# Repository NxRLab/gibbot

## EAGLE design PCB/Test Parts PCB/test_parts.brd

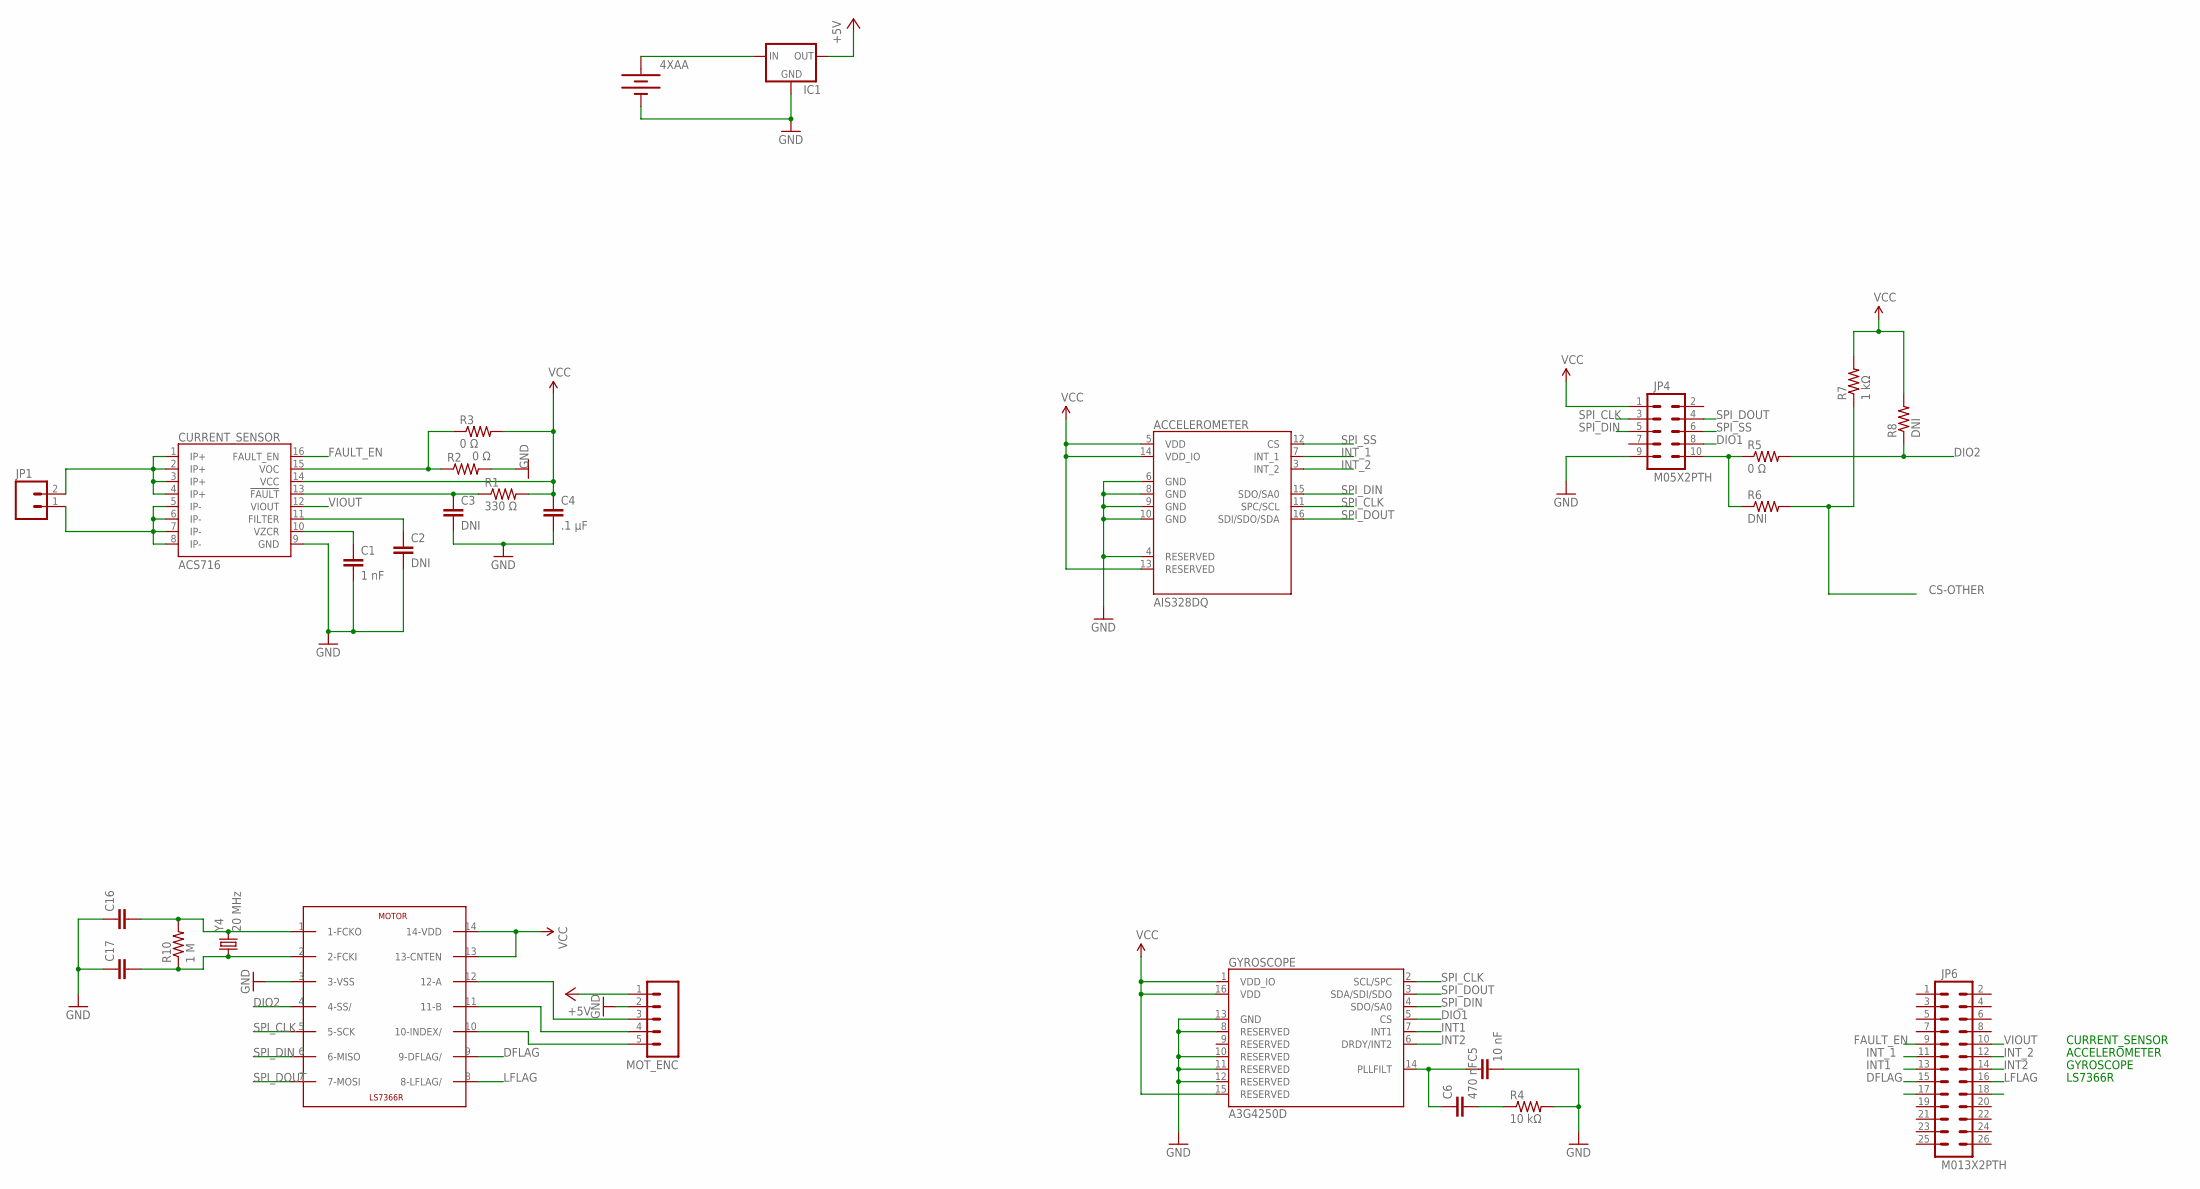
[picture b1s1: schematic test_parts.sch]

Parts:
4XAA: BATTERYTOP; BH4AA-PC
ACCELEROMETER: AIS328DQ; QFPN-24
C1: 1 nF; 0603-CAP
C2, C3: DNI; 0603-CAP
C4: .1 µF; 0603-CAP
C5: 10 nF; 0603-CAP
C6: 470 nF; 0603-CAP
C16, C17: CAP0603-CAP; 0603-CAP
CURRENT_SENSOR: ACS716; SOICW
GYROSCOPE: A3G4250D; LGA-16
IC1: V_REG_78XX-TO-220; TO-220-ALT
JP1: M02PTH; 1X02
JP4: M05X2PTH; AVR_ICSP
JP6: M013X2PTH; AVR_ICSP
MOTOR: LS7366R; SO14
MOT_ENC: M05PTH; 1X05
R1: 330 Ω; 0603-RES
R2, R3, R5: 0 Ω; 0603-RES
R4: 10 kΩ; 0603-RES
R6, R8: DNI; 0603-RES
R7: 1 kΩ; 0603-RES
R10: 1 M; R0603
Y4: 20 MHz; HC49US

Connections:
+5V: IC1.OUT, MOT_ENC.1
CS-OTHER: R6.2, R7.1
DFLAG: JP6.15, MOTOR.9 (9-DFLAG/)
DIO1: GYROSCOPE.5 (CS), JP4.8
DIO2: MOTOR.4 (4-SS/), R5.2, R8.1
FAULT_EN: CURRENT_SENSOR.16 (FAULT_EN), JP6.9
GND: 4XAA.-, ACCELEROMETER.4 (RESERVED), ACCELEROMETER.6 (GND), ACCELEROMETER.8 (GND), ACCELEROMETER.9 (GND), ACCELEROMETER.10 (GND), C1.2, C2.2, C3.2, C4.2, C5.2, C16.1, C17.1, CURRENT_SENSOR.9 (GND), GYROSCOPE.8 (RESERVED), GYROSCOPE.10 (RESERVED), GYROSCOPE.11 (RESERVED), GYROSCOPE.12 (RESERVED), GYROSCOPE.13 (GND), IC1.GND, JP4.9, MOTOR.3 (3-VSS), MOT_ENC.2, R2.2, R4.2
INT1: GYROSCOPE.7 (INT1), JP6.13
INT2: GYROSCOPE.6 (DRDY/INT2), JP6.14
INT_1: ACCELEROMETER.7 (INT_1), JP6.11
INT_2: ACCELEROMETER.3 (INT_2), JP6.12
LFLAG: JP6.16, MOTOR.8 (8-LFLAG/)
unnamed: CURRENT_SENSOR.1 (IP+), CURRENT_SENSOR.2 (IP+), CURRENT_SENSOR.3 (IP+), CURRENT_SENSOR.4 (IP+), JP1.2
unnamed: CURRENT_SENSOR.5 (IP-), CURRENT_SENSOR.6 (IP-), CURRENT_SENSOR.7 (IP-), CURRENT_SENSOR.8 (IP-), JP1.1
unnamed: C3.1, CURRENT_SENSOR.13 (!FAULT), R1.1
unnamed: C1.1, CURRENT_SENSOR.10 (VZCR)
unnamed: C2.1, CURRENT_SENSOR.11 (FILTER)
unnamed: CURRENT_SENSOR.15 (VOC), R2.1, R3.1
unnamed: JP4.10, R5.1, R6.1
unnamed: 4XAA.+, IC1.IN
unnamed: C5.1, C6.1, GYROSCOPE.14 (PLLFILT)
unnamed: C6.2, R4.1
unnamed: C16.2, MOTOR.1 (1-FCKO), R10.2, Y4.2
unnamed: C17.2, MOTOR.2 (2-FCKI), R10.1, Y4.1
unnamed: MOTOR.12 (12-A), MOT_ENC.3
unnamed: MOTOR.11 (11-B), MOT_ENC.4
unnamed: MOTOR.10 (10-INDEX/), MOT_ENC.5
SPI_CLK: ACCELEROMETER.11 (SPC/SCL), GYROSCOPE.2 (SCL/SPC), JP4.3, MOTOR.5 (5-SCK)
SPI_DIN: ACCELEROMETER.15 (SDO/SA0), GYROSCOPE.4 (SDO/SA0), JP4.5, MOTOR.6 (6-MISO)
SPI_DOUT: ACCELEROMETER.16 (SDI/SDO/SDA), GYROSCOPE.3 (SDA/SDI/SDO), JP4.4, MOTOR.7 (7-MOSI)
SPI_SS: ACCELEROMETER.12 (CS), JP4.6
VCC: ACCELEROMETER.5 (VDD), ACCELEROMETER.13 (RESERVED), ACCELEROMETER.14 (VDD_IO), C4.1, CURRENT_SENSOR.14 (VCC), GYROSCOPE.1 (VDD_IO), GYROSCOPE.15 (RESERVED), GYROSCOPE.16 (VDD), JP4.1, MOTOR.13 (13-CNTEN), MOTOR.14 (14-VDD), R1.2, R3.2, R7.2, R8.2
VIOUT: CURRENT_SENSOR.12 (VIOUT), JP6.10

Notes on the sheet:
CURRENT_SENSOR
ACCELEROMETER
GYROSCOPE
LS7366R

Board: 2 copper layers, 28 parts (1 on the bottom side), 33 nets, no tracks yet.

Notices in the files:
parts and their libraries:
SparkFun: Licensing: CC v3.0 Share-Alike You are welcome to use this library for commercial purposes.
